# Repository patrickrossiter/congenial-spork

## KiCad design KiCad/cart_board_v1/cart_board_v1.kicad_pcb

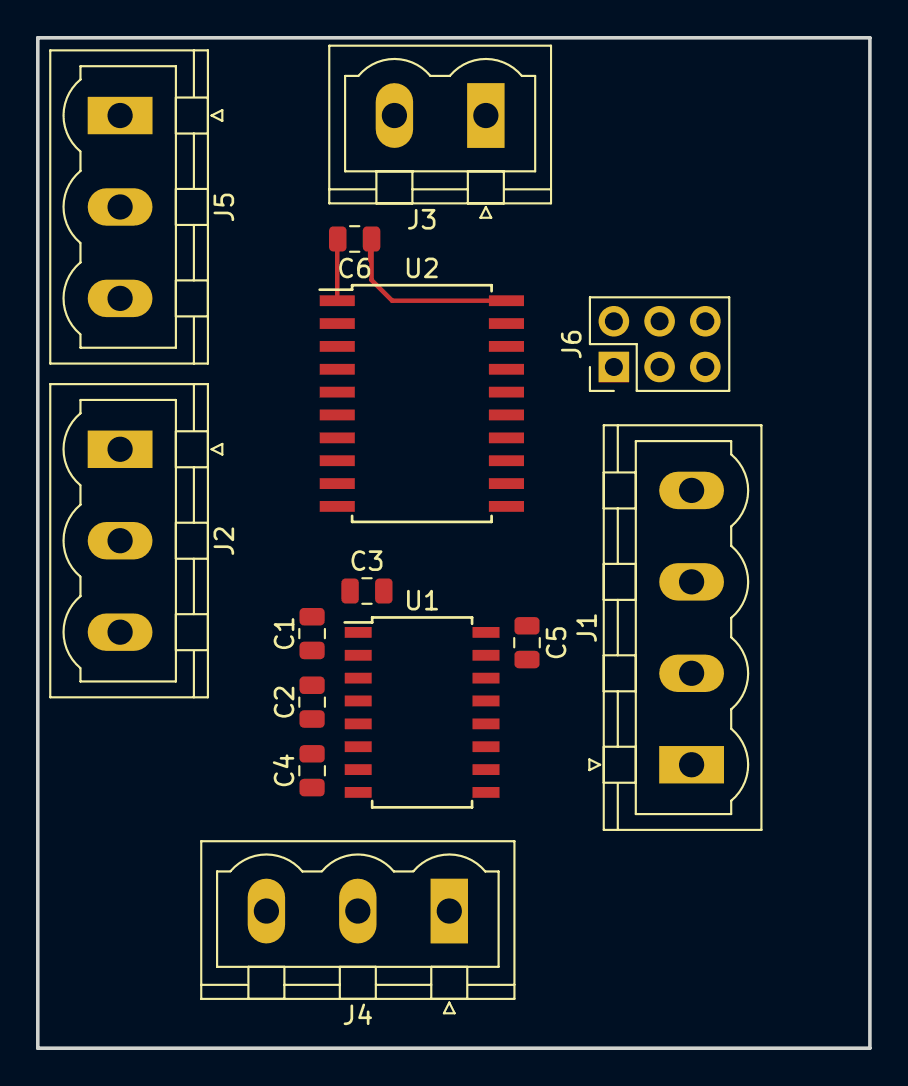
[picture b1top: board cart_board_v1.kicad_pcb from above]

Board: 2 copper layers, 46.2 x 56.1 mm, 14 parts (0 on the bottom side), 19 nets.

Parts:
C1, C2, C3, C4, C5: 1u; C_0805_2012Metric
C6: 100n; C_0805_2012Metric
J1: Limit Switch Inputs; PhoenixContact_MSTBVA_2,5_4-G-5,08_1x04_P5.08mm_Vertical
J2: DC Motor Control; PhoenixContact_MSTBVA_2,5_3-G-5,08_1x03_P5.08mm_Vertical
J3: Battery Input; PhoenixContact_MSTBVA_2,5_2-G-5,08_1x02_P5.08mm_Vertical
J4: USART Connection; PhoenixContact_MSTBVA_2,5_3-G-5,08_1x03_P5.08mm_Vertical
J5: Rotor Position Sensor; PhoenixContact_MSTBVA_2,5_3-G-5,08_1x03_P5.08mm_Vertical
J6: Programming Header; PinHeader_2x03_P2.54mm_Vertical
U1: MAX232; SOIC-16W_5.3x10.2mm_P1.27mm
U2: ATtiny816-SN; SOIC-20W_7.5x12.8mm_P1.27mm

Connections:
+5V: C3.2, C5.1, C6.2, J1.1, J3.1, J6.2, U1.16, U2.1
/RXD: U1.12, U2.8
/TXD: U1.10, U2.9
GNDD: C4.1, C5.2, C6.1, J1.2, J2.3, J3.2, J4.1, J5.3, J6.6, U1.15, U2.20
unnamed: C1.1, U1.1
unnamed: C1.2, U1.3
unnamed: C2.1, U1.4
unnamed: C2.2, U1.5
unnamed: C3.1, U1.2
unnamed: C4.2, U1.6
unnamed: J1.3, U2.12
unnamed: J1.4, U2.13
unnamed: J2.1, U2.11
unnamed: J2.2, U2.10
unnamed: J4.2, U1.13
unnamed: J4.3, U1.7
unnamed: J5.1, U2.4
unnamed: J5.2, U2.5
unnamed: J6.1, U2.16

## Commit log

2020-09-29 Initial commit
    Nothing in here should be used for anything.
2020-10-02 Functional bang-bang stabiliser for non-inverted pendulum
    Everything working as expected up to this point
2020-10-03 Final version - stabilise a non-inverted pendulum
